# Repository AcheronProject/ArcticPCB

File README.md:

# Acheron 60-SM-S-STM32-MX-TH-WI (Codename "ArcticPCB")

See [this page](https://gondolindrim.github.io/AcheronDocs/arctic/intro.html) for the ArcticPCB documentation.

## Introduction

Arctic is an STM32F072-based universal 60% keyboard PCB featuring limited layouts and features. The layouts were cherry-picked by enthusiast ArcticFox and consist of only Tsangan bottom row. 

This PCB also features "relief" flex cuts aimed at improving keyboard typing feeling.

Arctic hold a very special place in my heart as it was one of the first two PCBs, together with the KeebsPCB, in the Acheron Project and effectively inaugurated it.

## Contributors

- Raphael "ArcticFox" Hochheim for helping choosing the compatible layouts
- Felipe 'MrKeebs" Coury who paid for the V1 prototypes and helped immensely by funding my learning
- PCBWay for sponsoring the pre-revision Alpha prototypes

## Supported layouts

Click [this link](http://www.keyboard-layout-editor.com/#/gists/73be427d3e8086a9253feece2dae6974) for the KLE file for the Arctic.

## Renders

Click at the images to zoom in.

Renders generated by the [tracespace.io](https://tracespace.io/view/) site.

## PCBWay sponsorship

The pre-revision Alpha of the ArcticPCB was sponsored by [PCBWay](http://www.pcbway.com), a big asian PCB manufacturer that provided prototypes for the Arctic.

The review article can be found at [the AcheronDocs page](https://gondolindrim.github.io/AcheronDocs/pcbway/sponsorship.html).

## Icon

The Fox icon was based on [this design](https://www.flaticon.com/free-icon/fox_112476) and slightly modified.

## Copyright notice

This project is released under the Acheron Open-Hardware License V1.2. For the license, please refer to the LICENCE.md file.

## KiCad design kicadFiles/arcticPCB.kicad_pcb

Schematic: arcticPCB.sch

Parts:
CB1: 1uF; C_0402_1005Metric
CB2: 10n; C_0402_1005Metric
CB3, CB5, CB8: 100n; C_0402_1005Metric
CB4, CB6: 4.7uF; C_0402_1005Metric
CB7: 100nF; C_0402_1005Metric
CRST1: 10u; C_0805_2012Metric_Pad1.15x1.40mm_HandSolder
CRST2: 4.7n; C_0805_2012Metric_Pad1.15x1.40mm_HandSolder
CSH1, CSH2: 4.7nF; C_0805_2012Metric
CSI1: 100n; C_0805_2012Metric_Pad1.15x1.40mm_HandSolder
CSO1: 100n; C_0805_2012Metric_Pad1.15x1.40mm_HandSolder
CUSB1: 100n; C_0805_2012Metric_Pad1.15x1.40mm_HandSolder
D1, D2, D3, D4, D5, D6, D7, D8, D9, D10, D11, D12, D13, D14, D15, D16, D17, D18, D19, D20, D21, D22, D23, D24, D25, D26, D27, D28, D29, D30, D31, D32, D33, D34, D35, D36, D37, D38, D39, D40, D41, D42, D43, D44, D45, D46, D47, D48, D49, D50, D51, D52, D53, D54, D55, D56, D57, D58, D59, D60, D62, D65: 1N4148; D_SOD-123
DF1: RB060M-60TR; D_SOD-123
DRST1: 1N4148; D_SOD-123
DS1: 1N4148; D_SOD-123
DSH1: 1N4007; D_SOD-123
F1: Polyfuse; Fuse_1812_4532
H1, H6: Half Side Hole; halfSideHole
H2: Mounting Hole; MoutingHole_Oval_7mm_5.0x2.5mm
H3, H4, H5, H7, H8, H9, H10: Oval Mounting Hole; MoutingHole_Oval_7mm_5.0x2.5mm
J1: TYPE-C-31-M12_13; TYPE-C-31-M-12
J2: Conn_01x14; PinHeader_1x14_P2.54mm_Vertical
J3: Conn_ARM_JTAG_SWD_10
L1: ArcticLogo; arcticLogoFilled
L2: OSHLogo; osh-logo
L3: Acheron Logo; acheronLong
L4: ArcticLabel; arcticLabel
L5: Acheron Logo; arcticLabelMask
QRST1: DTC123J; SOT-23
RCC1, RCC2: 5.1k; R_SMD_1026
RRST1: 100k; R_SMD_1026
RSH1, RSH2: 1M; R_SMD_1026
SW1: ESC; MX100
SW2: 1; MX100
SW3: 2; MX100
SW4: 3; MX100
SW5: 4; MX100
SW6: 5; MX100
SW7: 6; MX100
SW8: 7; MX100
SW9: 8; MX100
SW10: 9; MX100
SW11: 0; MX100
SW12: -_; MX100
SW13: +=; MX100
SW14: 2U BKSP; MX200
SW15: TAB_150; MX150
SW16: Q; MX100
SW17: W; MX100
SW18: E; MX100
SW19: R; MX100
SW20: T; MX100
SW21: Y; MX100
SW22: U; MX100
SW23: I; MX100
SW24: O; MX100
SW25: P; MX100
SW26: [{; MX100
SW27: ]}; MX100
SW28: \\|_150; MX150
SW29: CAPS_175; MX175
SW30: A; MX100
SW31: S; MX100
SW32: D; MX100
SW33: F; MX100
SW34: G; MX100
SW35: H; MX100
SW36: J; MX100
SW37: K; MX100
SW38: L; MX100
SW39: :;; MX100
SW40: \"'; MX100
SW41: ENTER_225; MX225R
SW42: LSHIFT_225; MX225
SW43: Z; MX100
SW44: X; MX100
SW45: C; MX100
SW46: V; MX100
SW47: B; MX100
SW48: N; MX100
SW49: M; MX100
SW50: <,; MX100
SW51: >.; MX100
SW52: ?/; MX100
SW53: RSHIFT_275; MX275
SW54: LCTRL_150; MX150
SW55: LGUI_100; MX100
SW56: LALT_150; MX150
SW57: SPACE_7U; MX700R
SW58: RALT_150; MX150
SW59: RGUI_100; MX100
SW60: RCTRL_150; MX150
SW61: FN_100; MX100
SW62: RSHIFT_175; MX175
SW63: STEPPED_CAPS_125; MX125
SW64: 1U LBKSP; MX100
SW65: 1U RBKSP; MX100
SWRST1: SW_Push; smdPushBtn
U1: STM32F072-LQFP48; LQFP-48_7x7mm_P0.5mm
U2: USBLC6-2SC6; SOT-23-6
U3: MCP1700-3302E_SOT23; SOT-23

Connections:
3.3V: CB1.2, CB2.2, CB3.2, CB4.2, CB5.2, CB6.2, CB7.1, CB8.2, CSO1.2, DS1.2 (A), J3.1 (VTref), SWRST1.1, U1.1 (VBAT), U1.9 (VDDA), U1.24 (VDD), U1.36 (VDDIO2), U1.48 (VDD), U3.2 (VO)
5V: CSI1.2, DF1.1 (K), DS1.1 (K), F1.1, U3.3 (VI)
/SHIELD: CSH1.2, J1.S (SHIELD), RSH1.1
BOOT0: CRST1.2, DRST1.1 (K), RRST1.1, U1.44 (BOOT0)
CASE: DSH1.2 (A), H8.1
Col1: SW1.1 (Col), SW15.1 (Col), SW29.1 (Col), SW42.1 (Col), SW54.1 (Col), SW63.1 (Col), U1.18 (PB0/TIM3_CH3/ADC_IN8)
Col2: SW2.1 (Col), SW16.1 (Col), SW30.1 (Col), SW43.1 (Col), SW55.1 (Col), U1.15 (PA5/ADC_IN5/DAC_OUT2)
Col3: SW3.1 (Col), SW17.1 (Col), SW31.1 (Col), SW44.1 (Col), SW56.1 (Col), U1.14 (PA4/TIM14_CH1/ADC_IN4)
Col4: SW4.1 (Col), SW18.1 (Col), SW32.1 (Col), SW45.1 (Col), U1.13 (PA3/TIM15_CH2/ADC_IN3)
Col5: SW5.1 (Col), SW19.1 (Col), SW33.1 (Col), SW46.1 (Col), U1.12 (PA2/ADC_IN2)
Col6: SW6.1 (Col), SW20.1 (Col), SW34.1 (Col), SW47.1 (Col), U1.11 (PA1/ADC_IN1)
Col7: SW7.1 (Col), SW21.1 (Col), SW35.1 (Col), SW48.1 (Col), SW57.1 (Col), U1.10 (PA0/ADC_IN0)
Col8: SW8.1 (Col), SW22.1 (Col), SW36.1 (Col), SW49.1 (Col), U1.6 (PF1/OSC_OUT)
Col9: SW9.1 (Col), SW23.1 (Col), SW37.1 (Col), SW50.1 (Col), U1.5 (PF0/OSC_IN)
Col10: SW10.1 (Col), SW24.1 (Col), SW38.1 (Col), SW51.1 (Col), SW58.1 (Col), U1.4 (PC15/OSC32_OUT)
Col11: SW11.1 (Col), SW25.1 (Col), SW39.1 (Col), SW52.1 (Col), SW59.1 (Col), U1.3 (PC14/OSC32_IN)
Col12: SW12.1 (Col), SW26.1 (Col), SW40.1 (Col), SW53.1 (Col), SW60.1 (Col), SW62.1 (Col), U1.2 (PC13)
Col13: SW13.1 (Col), SW27.1 (Col), SW41.1 (Col), SW61.1 (Col), U1.46 (SPI2_NSS/I2S2_WS/I2C1_SDA/TIM17_CH1/PB9)
Col14: SW14.1 (Col), SW28.1 (Col), SW64.1 (Col), SW65.1 (Col), U1.45 (I2C1_SCL/TIM16_CH1/PB8)
D+: U1.33 (USB_DP/PA12), U2.3 (IO2)
D-: U1.32 (USB_DM/TIM1_CH4/PA11), U2.1 (IO1)
DBus+: J1.A6 (D+), J1.B6 (D+), U2.4 (IO2)
DBus-: J1.A7 (D-), J1.B7 (D-), U2.6 (IO1)
Extra1: J2.1, U1.41 (SPI1_MOSI/I2S1_SD/TIM3_CH2/PB5)
Extra2: J2.2, U1.40 (SPI1_MISO/I2S1_MCK/TIM3_CH1/PB4)
Extra3: J2.3, U1.39 (SPI1_SCK/I2S1_CK/TIM2_CH2/PB3)
Extra4: J2.4, U1.38 (PA2)
Extra5: J2.5, U1.31 (TIM1_CH3/PA10)
Extra6: J2.6, U1.30 (TIM1_CH2/PA9)
Extra7: J2.7, U1.29 (TIM1_CH1/PA8)
Extra8: J2.8, U1.28 (SPI2_MOSI/I2S2_SD/PB15)
Extra9: J2.9, U1.27 (PB14/SPI2_MISO/I2S2_MCK/I2C2_SDA/TIM15_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)
Extra10: J2.10, U1.26 (SPI2_SCK/I2S2_CK/I2C2_SCL/PB13)
Extra11: J2.11, U1.25 (PB12)
Extra12: J2.12, U1.22 (PB11/TIM2_CH4/I2C2_SDA)
Extra13: J2.13, U1.21 (PB10/SPI2_SCK/I2C2_SCL/TIM2_CH3)
Extra14: J2.14, U1.20 (PB2)
GND: CB1.1, CB2.1, CB3.1, CB4.1, CB5.1, CB6.1, CB7.2, CB8.1, CRST1.1, CRST2.2, CSH1.1, CSH2.1, CSI1.1, CSO1.1, CUSB1.1, DF1.2 (A), J1.A1 (GND), J1.B1 (GND), J3.3 (GND), J3.5 (GND), J3.9 (GNDDetect), QRST1.2 (E), RCC1.1, RCC2.1, RRST1.2, RSH1.2, RSH2.2, U1.8 (VSSA), U1.23 (VSS), U1.35 (VSS), U1.47 (VSS), U2.2 (GND), U3.1 (GND)
NRST: CRST2.1, J3.10 (~RESET~), QRST1.3 (C), U1.7 (NRST)
unnamed: CSH2.2, DSH1.1 (K), RSH2.1
unnamed: D1.2 (A), SW1.2 (Row)
unnamed: D2.2 (A), SW2.2 (Row)
unnamed: D3.2 (A), SW3.2 (Row)
unnamed: D4.2 (A), SW4.2 (Row)
unnamed: D5.2 (A), SW5.2 (Row)
unnamed: D6.2 (A), SW6.2 (Row)
unnamed: D7.2 (A), SW7.2 (Row)
unnamed: D8.2 (A), SW8.2 (Row)
unnamed: D9.2 (A), SW9.2 (Row)
unnamed: D10.2 (A), SW10.2 (Row)
unnamed: D11.2 (A), SW11.2 (Row)
unnamed: D12.2 (A), SW12.2 (Row)
unnamed: D13.2 (A), SW13.2 (Row)
unnamed: D14.2 (A), SW14.2 (Row), SW64.2 (Row)
unnamed: D15.2 (A), SW15.2 (Row)
unnamed: D16.2 (A), SW16.2 (Row)
unnamed: D17.2 (A), SW17.2 (Row)
unnamed: D18.2 (A), SW18.2 (Row)
unnamed: D19.2 (A), SW19.2 (Row)
unnamed: D20.2 (A), SW20.2 (Row)
unnamed: D21.2 (A), SW21.2 (Row)
unnamed: D22.2 (A), SW22.2 (Row)
unnamed: D23.2 (A), SW23.2 (Row)
unnamed: D24.2 (A), SW24.2 (Row)
unnamed: D25.2 (A), SW25.2 (Row)
unnamed: D26.2 (A), SW26.2 (Row)
unnamed: D27.2 (A), SW27.2 (Row)
unnamed: D28.2 (A), SW28.2 (Row)
unnamed: D29.2 (A), SW29.2 (Row), SW63.2 (Row)
unnamed: D30.2 (A), SW30.2 (Row)
unnamed: D31.2 (A), SW31.2 (Row)
unnamed: D32.2 (A), SW32.2 (Row)
unnamed: D33.2 (A), SW33.2 (Row)
unnamed: D34.2 (A), SW34.2 (Row)
unnamed: D35.2 (A), SW35.2 (Row)
unnamed: D36.2 (A), SW36.2 (Row)
unnamed: D37.2 (A), SW37.2 (Row)
unnamed: D38.2 (A), SW38.2 (Row)
unnamed: D39.2 (A), SW39.2 (Row)
unnamed: D40.2 (A), SW40.2 (Row)
unnamed: D41.2 (A), SW41.2 (Row)
unnamed: D42.2 (A), SW42.2 (Row)
unnamed: D43.2 (A), SW43.2 (Row)
unnamed: D44.2 (A), SW44.2 (Row)
unnamed: D45.2 (A), SW45.2 (Row)
unnamed: D46.2 (A), SW46.2 (Row)
unnamed: D47.2 (A), SW47.2 (Row)
unnamed: D48.2 (A), SW48.2 (Row)
unnamed: D49.2 (A), SW49.2 (Row)
unnamed: D50.2 (A), SW50.2 (Row)
unnamed: D51.2 (A), SW51.2 (Row)
unnamed: D52.2 (A), SW52.2 (Row)
unnamed: D53.2 (A), SW61.2 (Row)
unnamed: D54.2 (A), SW54.2 (Row)
unnamed: D55.2 (A), SW55.2 (Row)
unnamed: D56.2 (A), SW56.2 (Row)
unnamed: D57.2 (A), SW57.2 (Row)
unnamed: D58.2 (A), SW58.2 (Row)
unnamed: D59.2 (A), SW59.2 (Row)
unnamed: D60.2 (A), SW60.2 (Row)
unnamed: D62.2 (A), SW53.2 (Row), SW62.2 (Row)
unnamed: D65.2 (A), SW65.2 (Row)
unnamed: DRST1.2 (A), QRST1.1 (B), SWRST1.2
unnamed: J1.A5 (CC1), RCC2.2
unnamed: J1.B5 (CC2), RCC1.2
Row1: D1.1 (K), D2.1 (K), D3.1 (K), D4.1 (K), D5.1 (K), D6.1 (K), D7.1 (K), D8.1 (K), D9.1 (K), D10.1 (K), D11.1 (K), D12.1 (K), D13.1 (K), D14.1 (K), U1.43 (2C1_SDA/PB7)
Row2: D15.1 (K), D16.1 (K), D17.1 (K), D18.1 (K), D19.1 (K), D20.1 (K), D21.1 (K), D22.1 (K), D23.1 (K), D24.1 (K), D25.1 (K), D26.1 (K), D27.1 (K), D28.1 (K), U1.42 (I2C1_SCL/PB6)
Row3: D29.1 (K), D30.1 (K), D31.1 (K), D32.1 (K), D33.1 (K), D34.1 (K), D35.1 (K), D36.1 (K), D37.1 (K), D38.1 (K), D39.1 (K), D40.1 (K), D41.1 (K), D65.1 (K), U1.16 (PA6/ADC_IN6/TIM3_CH1/TIM16_CH1)
Row4: D42.1 (K), D43.1 (K), D44.1 (K), D45.1 (K), D46.1 (K), D47.1 (K), D48.1 (K), D49.1 (K), D50.1 (K), D51.1 (K), D52.1 (K), D53.1 (K), D62.1 (K), U1.17 (PA7/TIM3_CH2/TIM14_CH1/ADC_IN7)
Row5: D54.1 (K), D55.1 (K), D56.1 (K), D57.1 (K), D58.1 (K), D59.1 (K), D60.1 (K), U1.19 (PB1/TIM3_CH4/TIM14_CH1/ADC_IN9)
SWCLK: J3.4 (SWDCLK/TCK), U1.37 (SWCLK/PA14)
SWDIO: J3.2 (SWDIO/TMS), U1.34 (SWDIO/PA13)
VBUS: CUSB1.2, F1.2, J1.A4 (VBUS), J1.B4 (VBUS), U2.5 (VBUS)

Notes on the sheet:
REFERENCES
[1] STM32F072x8 / STM32F072xB datasheet
https://www.st.com/resource/en/datasheet/stm32f072rb.pdf
[2] AN4080 Application note
https://www.st.com/content/ccc/resource/technical/document/application_note/c9/19/d7/b8/6b/0e/4c/d3/DM00051986.pdf/files/DM00051986.pdf/jcr:content/translations/en.DM00051986.pdf
Switch matrix
Logos and flags
Mounting holes
Shield
USB Connector
USD ESD
Power supply and protection circuit
Serial programming
Hard reset circuit
Case ESD
Extra pins
CBx are the bypass capacitors. Their value is specified in reference [2].
MCU

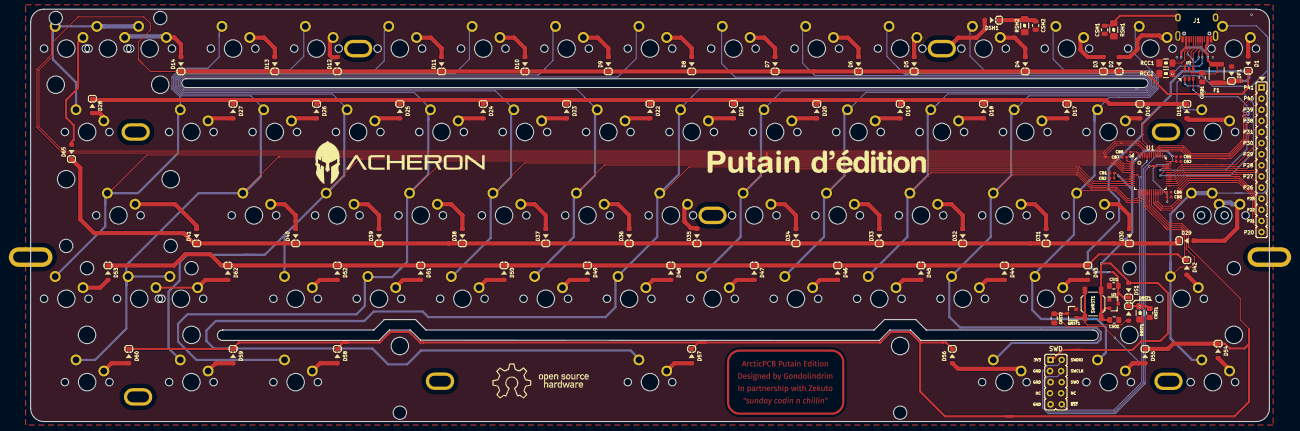
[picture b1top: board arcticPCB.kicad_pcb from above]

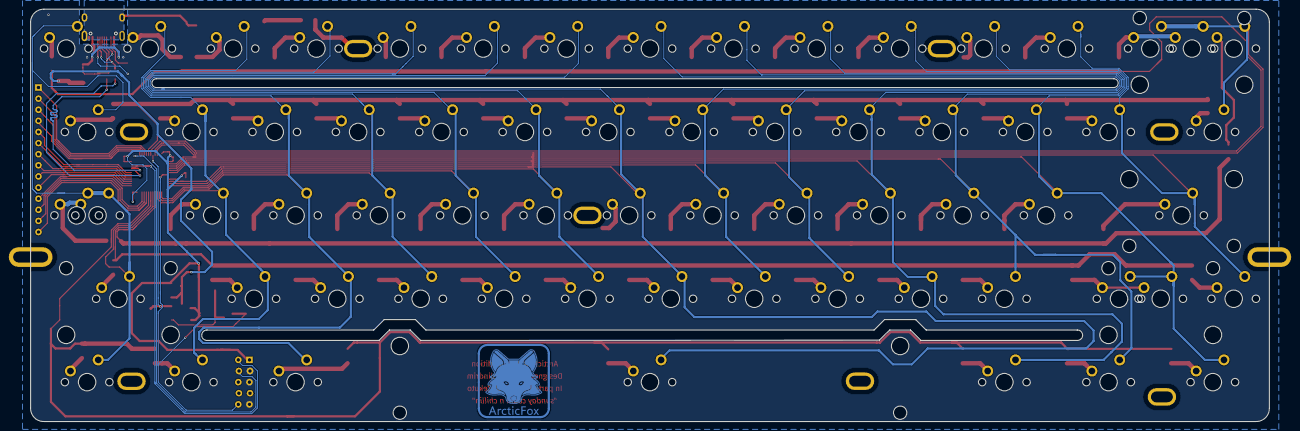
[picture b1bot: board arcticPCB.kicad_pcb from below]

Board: 2 copper layers, 283.0 x 94.2 mm, 176 parts (7 on the bottom side), 113 nets.

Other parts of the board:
L6: Putain Logo; putainLogo_50_5

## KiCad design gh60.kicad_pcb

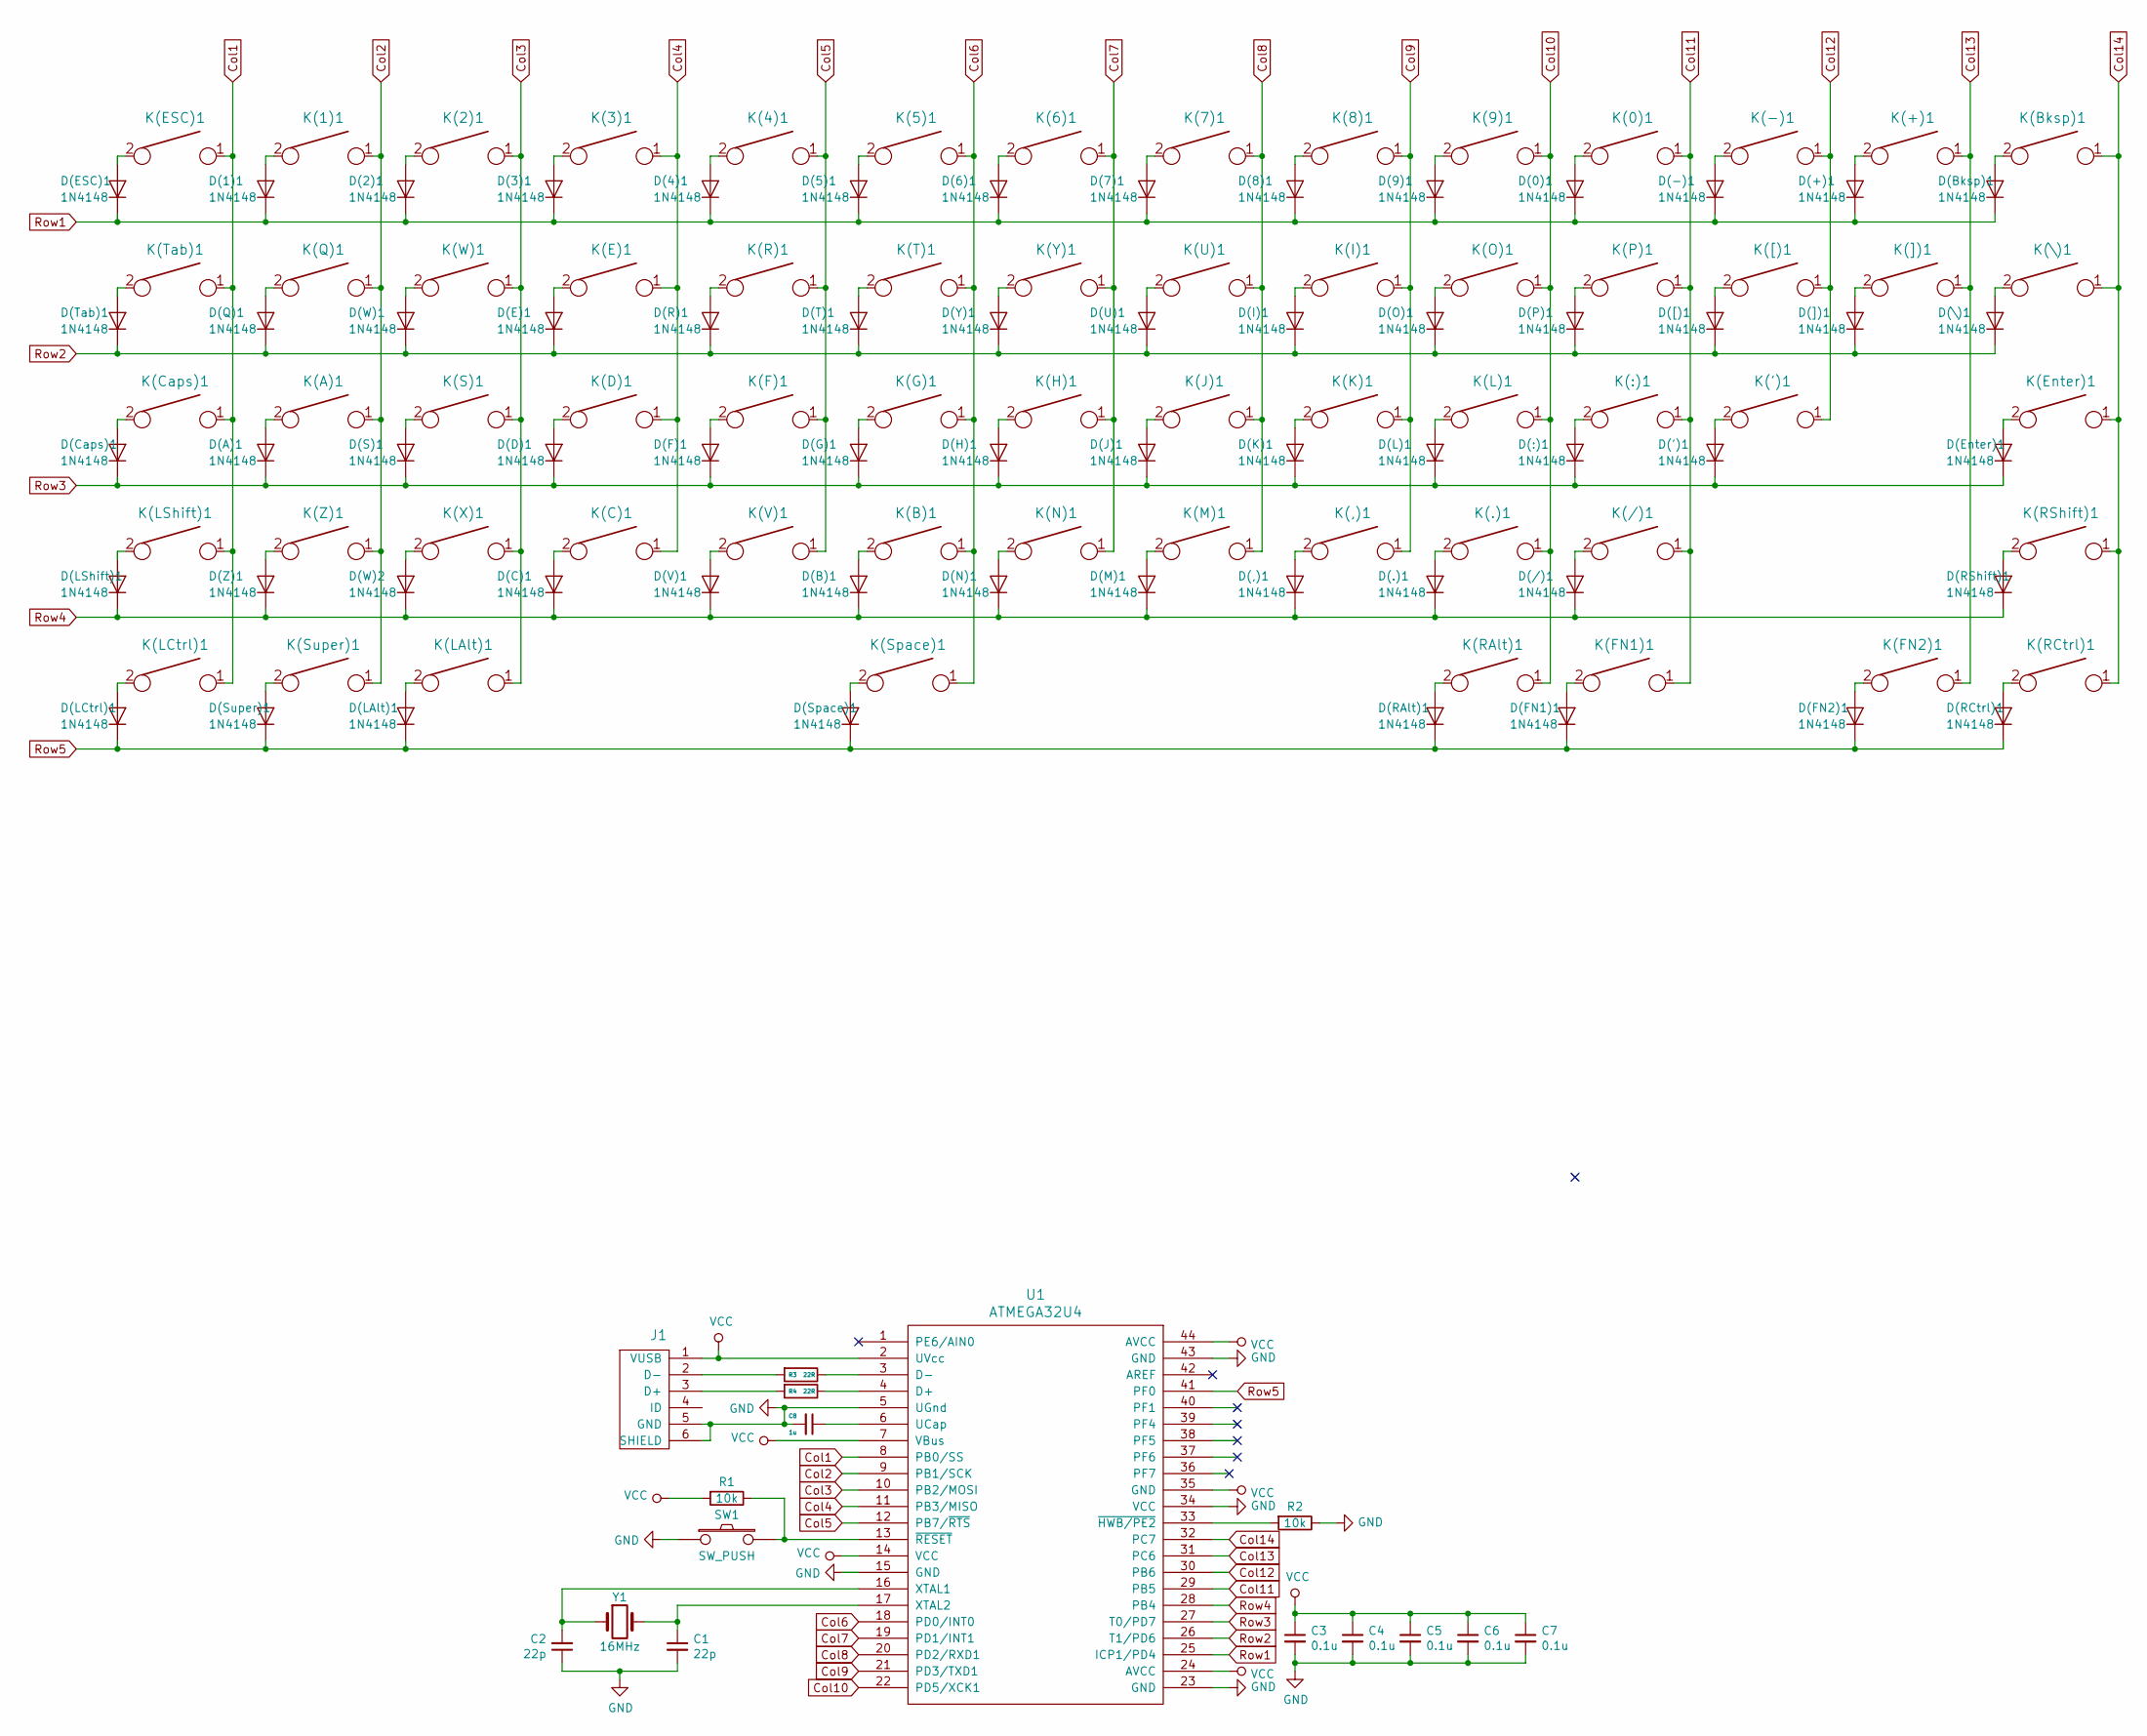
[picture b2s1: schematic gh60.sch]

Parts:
C1, C2: 22p; C_0805_2012Metric_Pad1.15x1.40mm_HandSolder
C3, C4, C5, C6, C7: 0.1u; C_0805_2012Metric_Pad1.15x1.40mm_HandSolder
C8: 1u; C_0805_2012Metric_Pad1.15x1.40mm_HandSolder
D(0)1, D(1)1, D(2)1, D(3)1, D(4)1, D(5)1, D(6)1, D(7)1, D(8)1, D(9)1, D(.)1: 1N4148; D_SOD123_axial
D(')1: 1N4148; D_SOD123_axial
D(+)1: 1N4148; D_SOD123_axial
D(,)1: 1N4148; D_SOD123_axial
D(-)1: 1N4148; D_SOD123_axial
D(/)1: 1N4148; D_SOD123_axial
D(:)1: 1N4148; D_SOD123_axial
D(A)1: 1N4148; D_SOD123_axial
D(B)1: 1N4148; D_SOD123_axial
D(Bksp)1: 1N4148; D_SOD123_axial
D(C)1: 1N4148; D_SOD123_axial
D(Caps)1: 1N4148; D_SOD123_axial
D(D)1: 1N4148; D_SOD123_axial
D(E)1: 1N4148; D_SOD123_axial
D(ESC)1: 1N4148; D_SOD123_axial
D(Enter)1: 1N4148; D_SOD123_axial
D(F)1: 1N4148; D_SOD123_axial
D(FN1)1, D(FN2)1: 1N4148; D_SOD123_axial
D(G)1: 1N4148; D_SOD123_axial
D(H)1: 1N4148; D_SOD123_axial
D(I)1: 1N4148; D_SOD123_axial
D(J)1: 1N4148; D_SOD123_axial
D(K)1: 1N4148; D_SOD123_axial
D(L)1: 1N4148; D_SOD123_axial
D(LAlt)1: 1N4148; D_SOD123_axial
D(LCtrl)1: 1N4148; D_SOD123_axial
D(LShift)1: 1N4148; D_SOD123_axial
D(M)1: 1N4148; D_SOD123_axial
D(N)1: 1N4148; D_SOD123_axial
D(O)1: 1N4148; D_SOD123_axial
D(P)1: 1N4148; D_SOD123_axial
D(Q)1: 1N4148; D_SOD123_axial
D(R)1: 1N4148; D_SOD123_axial
D(RAlt)1: 1N4148; D_SOD123_axial
D(RCtrl)1: 1N4148; D_SOD123_axial
D(RShift)1: 1N4148; D_SOD123_axial
D(S)1: 1N4148; D_SOD123_axial
D(Space)1: 1N4148; D_SOD123_axial
D(Super)1: 1N4148; D_SOD123_axial
D(T)1: 1N4148; D_SOD123_axial
D(Tab)1: 1N4148; D_SOD123_axial
D(U)1: 1N4148; D_SOD123_axial
D(V)1: 1N4148; D_SOD123_axial
D(W)1, D(W)2: 1N4148; D_SOD123_axial
D(Y)1: 1N4148; D_SOD123_axial
D(Z)1: 1N4148; D_SOD123_axial
D([)1: 1N4148; D_SOD123_axial
D(\)1: 1N4148; D_SOD123_axial
D(])1: 1N4148; D_SOD123_axial
J1: USB_mini_micro_B; USB_miniB_hirose_5S8
K(0)1, K(1)1, K(2)1, K(3)1, K(4)1, K(5)1, K(6)1, K(7)1, K(8)1, K(9)1, K(.)1: KEYSW; Mx_Alps_100
K(')1: KEYSW; Mx_Alps_100
K(+)1: KEYSW; Mx_Alps_100
K(,)1: KEYSW; Mx_Alps_100
K(-)1: KEYSW; Mx_Alps_100
K(/)1: KEYSW; Mx_Alps_100
K(:)1: KEYSW; Mx_Alps_100
K(A)1: KEYSW; Mx_Alps_100
K(B)1: KEYSW; Mx_Alps_100
K(Bksp)1: KEYSW; Mx_Alps_200
K(C)1: KEYSW; Mx_Alps_100
K(Caps)1: KEYSW; Mx_Alps_175
K(D)1: KEYSW; Mx_Alps_100
K(E)1: KEYSW; Mx_Alps_100
K(ESC)1: KEYSW; Mx_Alps_100
K(Enter)1: KEYSW; Mx_Alps_225
K(F)1: KEYSW; Mx_Alps_100
K(FN1)1, K(FN2)1: KEYSW; Mx_Alps_125
K(G)1: KEYSW; Mx_Alps_100
K(H)1: KEYSW; Mx_Alps_100
K(I)1: KEYSW; Mx_Alps_100
K(J)1: KEYSW; Mx_Alps_100
K(K)1: KEYSW; Mx_Alps_100
K(L)1: KEYSW; Mx_Alps_100
K(LAlt)1: KEYSW; Mx_Alps_125
K(LCtrl)1: KEYSW; Mx_Alps_125
K(LShift)1: KEYSW; Mx_Alps_225
K(M)1: KEYSW; Mx_Alps_100
K(N)1: KEYSW; Mx_Alps_100
K(O)1: KEYSW; Mx_Alps_100
K(P)1: KEYSW; Mx_Alps_100
K(Q)1: KEYSW; Mx_Alps_100
K(R)1: KEYSW; Mx_Alps_100
K(RAlt)1: KEYSW; Mx_Alps_125
K(RCtrl)1: KEYSW; Mx_Alps_125
K(RShift)1: KEYSW; Mx_Alps_275
K(S)1: KEYSW; Mx_Alps_100
K(Space)1: KEYSW; Mx_Alps_625
K(Super)1: KEYSW; Mx_Alps_125
K(T)1: KEYSW; Mx_Alps_100
K(Tab)1: KEYSW; Mx_Alps_150
K(U)1: KEYSW; Mx_Alps_100
K(V)1: KEYSW; Mx_Alps_100
K(W)1: KEYSW; Mx_Alps_100
K(X)1: KEYSW; Mx_Alps_100
K(Y)1: KEYSW; Mx_Alps_100
K(Z)1: KEYSW; Mx_Alps_100
K([)1: KEYSW; Mx_Alps_100
K(\)1: KEYSW; Mx_Alps_150
K(])1: KEYSW; Mx_Alps_100
R1, R2: 10k; R_0805_2012Metric_Pad1.15x1.40mm_HandSolder
R3, R4: 22R; R_0805_2012Metric_Pad1.15x1.40mm_HandSolder
SW1: SW_PUSH; SW_SPST_TL3342
U1: ATMEGA32U4; TQFP-44_10x10mm_P0.8mm
Y1: 16MHz; Crystal_SMD_5032-2Pin_5.0x3.2mm_HandSoldering

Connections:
Col1: K(Caps)1.1, K(ESC)1.1, K(LCtrl)1.1, K(LShift)1.1, K(Tab)1.1, U1.8 (PB0/SS)
Col2: K(1)1.1, K(A)1.1, K(Q)1.1, K(Super)1.1, K(Z)1.1, U1.9 (PB1/SCK)
Col3: K(2)1.1, K(LAlt)1.1, K(S)1.1, K(W)1.1, K(X)1.1, U1.10 (PB2/MOSI)
Col4: K(3)1.1, K(C)1.1, K(D)1.1, K(E)1.1, U1.11 (PB3/MISO)
Col5: K(4)1.1, K(F)1.1, K(R)1.1, K(V)1.1, U1.12 (PB7/~RTS)
Col6: K(5)1.1, K(B)1.1, K(G)1.1, K(Space)1.1, K(T)1.1, U1.18 (PD0/INT0)
Col7: K(6)1.1, K(H)1.1, K(N)1.1, K(Y)1.1, U1.19 (PD1/INT1)
Col8: K(7)1.1, K(J)1.1, K(M)1.1, K(U)1.1, U1.20 (PD2/RXD1)
Col9: K(8)1.1, K(,)1.1, K(I)1.1, K(K)1.1, U1.21 (PD3/TXD1)
Col10: K(9)1.1, K(.)1.1, K(L)1.1, K(O)1.1, K(RAlt)1.1, U1.22 (PD5/XCK1)
Col11: K(0)1.1, K(/)1.1, K(:)1.1, K(FN1)1.1, K(P)1.1, U1.29 (PB5)
Col12: K(')1.1, K(-)1.1, K([)1.1, U1.30 (PB6)
Col13: K(+)1.1, K(FN2)1.1, K(])1.1, U1.31 (PC6)
Col14: K(Bksp)1.1, K(Enter)1.1, K(RCtrl)1.1, K(RShift)1.1, K(\)1.1, U1.32 (PC7)
GND: C1.2, C2.1, C3.2, C4.2, C5.2, C6.2, C7.2, C8.2, J1.5 (GND), J1.6 (SHIELD), R2.1, SW1.1, U1.5 (UGnd), U1.15 (GND), U1.23 (GND), U1.34 (VCC), U1.43 (GND)
unnamed: C1.1, U1.17 (XTAL2), Y1.2
unnamed: C2.2, U1.16 (XTAL1), Y1.1
unnamed: C8.1, U1.6 (UCap)
unnamed: D(0)1.2 (A), K(0)1.2
unnamed: D(1)1.2 (A), K(1)1.2
unnamed: D(2)1.2 (A), K(2)1.2
unnamed: D(3)1.2 (A), K(3)1.2
unnamed: D(4)1.2 (A), K(4)1.2
unnamed: D(5)1.2 (A), K(5)1.2
unnamed: D(6)1.2 (A), K(6)1.2
unnamed: D(7)1.2 (A), K(7)1.2
unnamed: D(8)1.2 (A), K(8)1.2
unnamed: D(9)1.2 (A), K(9)1.2
unnamed: D(')1.2 (A), K(')1.2
unnamed: D(+)1.2 (A), K(+)1.2
unnamed: D(,)1.2 (A), K(,)1.2
unnamed: D(-)1.2 (A), K(-)1.2
unnamed: D(.)1.2 (A), K(.)1.2
unnamed: D(/)1.2 (A), K(/)1.2
unnamed: D(:)1.2 (A), K(:)1.2
unnamed: D(A)1.2 (A), K(A)1.2
unnamed: D(B)1.2 (A), K(B)1.2
unnamed: D(Bksp)1.2 (A), K(Bksp)1.2
unnamed: D(C)1.2 (A), K(C)1.2
unnamed: D(Caps)1.2 (A), K(Caps)1.2
unnamed: D(D)1.2 (A), K(D)1.2
unnamed: D(E)1.2 (A), K(E)1.2
unnamed: D(ESC)1.2 (A), K(ESC)1.2
unnamed: D(Enter)1.2 (A), K(Enter)1.2
unnamed: D(F)1.2 (A), K(F)1.2
unnamed: D(FN1)1.2 (A), K(FN1)1.2
unnamed: D(FN2)1.2 (A), K(FN2)1.2
unnamed: D(G)1.2 (A), K(G)1.2
unnamed: D(H)1.2 (A), K(H)1.2
unnamed: D(I)1.2 (A), K(I)1.2
unnamed: D(J)1.2 (A), K(J)1.2
unnamed: D(K)1.2 (A), K(K)1.2
unnamed: D(L)1.2 (A), K(L)1.2
unnamed: D(LAlt)1.2 (A), K(LAlt)1.2
unnamed: D(LCtrl)1.2 (A), K(LCtrl)1.2
unnamed: D(LShift)1.2 (A), K(LShift)1.2
unnamed: D(M)1.2 (A), K(M)1.2
unnamed: D(N)1.2 (A), K(N)1.2
unnamed: D(O)1.2 (A), K(O)1.2
unnamed: D(P)1.2 (A), K(P)1.2
unnamed: D(Q)1.2 (A), K(Q)1.2
unnamed: D(R)1.2 (A), K(R)1.2
unnamed: D(RAlt)1.2 (A), K(RAlt)1.2
unnamed: D(RCtrl)1.2 (A), K(RCtrl)1.2
unnamed: D(RShift)1.2 (A), K(RShift)1.2
unnamed: D(S)1.2 (A), K(S)1.2
unnamed: D(Space)1.2 (A), K(Space)1.2
unnamed: D(Super)1.2 (A), K(Super)1.2
unnamed: D(T)1.2 (A), K(T)1.2
unnamed: D(Tab)1.2 (A), K(Tab)1.2
unnamed: D(U)1.2 (A), K(U)1.2
unnamed: D(V)1.2 (A), K(V)1.2
unnamed: D(W)1.2 (A), K(W)1.2
unnamed: D(W)2.2 (A), K(X)1.2
unnamed: D(Y)1.2 (A), K(Y)1.2
unnamed: D(Z)1.2 (A), K(Z)1.2
unnamed: D([)1.2 (A), K([)1.2
unnamed: D(\)1.2 (A), K(\)1.2
unnamed: D(])1.2 (A), K(])1.2
unnamed: J1.2 (D-), R3.2
unnamed: J1.3 (D+), R4.2
unnamed: R1.1, SW1.2, U1.13 (~RESET)
unnamed: R2.2, U1.33 (~HWB/PE2)
unnamed: R3.1, U1.3 (D-)
unnamed: R4.1, U1.4 (D+)
Row1: D(0)1.1 (K), D(1)1.1 (K), D(2)1.1 (K), D(3)1.1 (K), D(4)1.1 (K), D(5)1.1 (K), D(6)1.1 (K), D(7)1.1 (K), D(8)1.1 (K), D(9)1.1 (K), D(+)1.1 (K), D(-)1.1 (K), D(Bksp)1.1 (K), D(ESC)1.1 (K), U1.25 (ICP1/PD4)
Row2: D(E)1.1 (K), D(I)1.1 (K), D(O)1.1 (K), D(P)1.1 (K), D(Q)1.1 (K), D(R)1.1 (K), D(T)1.1 (K), D(Tab)1.1 (K), D(U)1.1 (K), D(W)1.1 (K), D(Y)1.1 (K), D([)1.1 (K), D(\)1.1 (K), D(])1.1 (K), U1.26 (T1/PD6)
Row3: D(')1.1 (K), D(:)1.1 (K), D(A)1.1 (K), D(Caps)1.1 (K), D(D)1.1 (K), D(Enter)1.1 (K), D(F)1.1 (K), D(G)1.1 (K), D(H)1.1 (K), D(J)1.1 (K), D(K)1.1 (K), D(L)1.1 (K), D(S)1.1 (K), U1.27 (T0/PD7)
Row4: D(,)1.1 (K), D(.)1.1 (K), D(/)1.1 (K), D(B)1.1 (K), D(C)1.1 (K), D(LShift)1.1 (K), D(M)1.1 (K), D(N)1.1 (K), D(RShift)1.1 (K), D(V)1.1 (K), D(W)2.1 (K), D(Z)1.1 (K), U1.28 (PB4)
Row5: D(FN1)1.1 (K), D(FN2)1.1 (K), D(LAlt)1.1 (K), D(LCtrl)1.1 (K), D(RAlt)1.1 (K), D(RCtrl)1.1 (K), D(Space)1.1 (K), D(Super)1.1 (K), U1.41 (PF0)
VCC: C3.1, C4.1, C5.1, C6.1, C7.1, J1.1 (VUSB), R1.2, U1.2 (UVcc), U1.7 (VBus), U1.14 (VCC), U1.24 (AVCC), U1.35 (GND), U1.44 (AVCC)

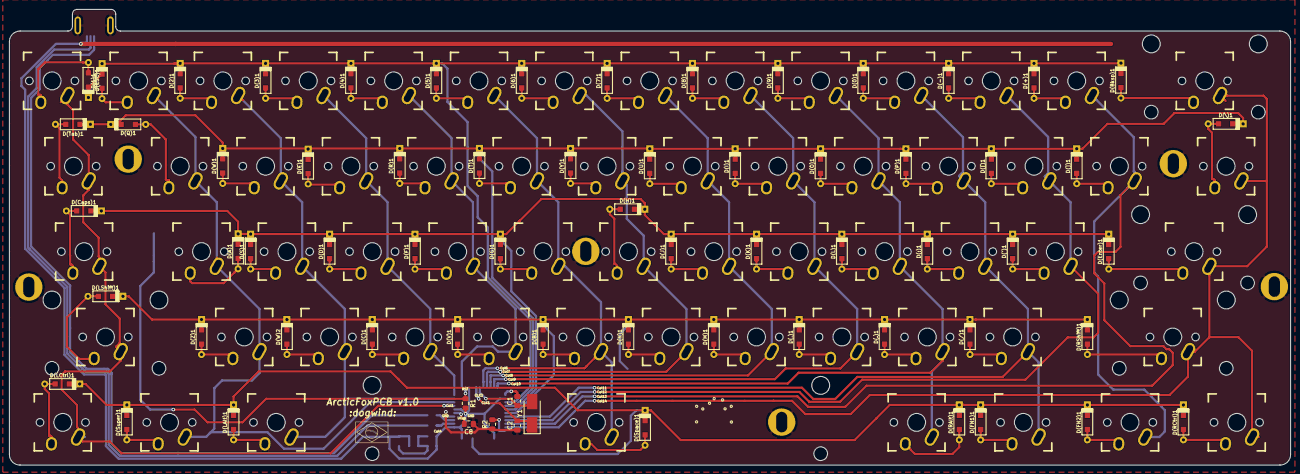
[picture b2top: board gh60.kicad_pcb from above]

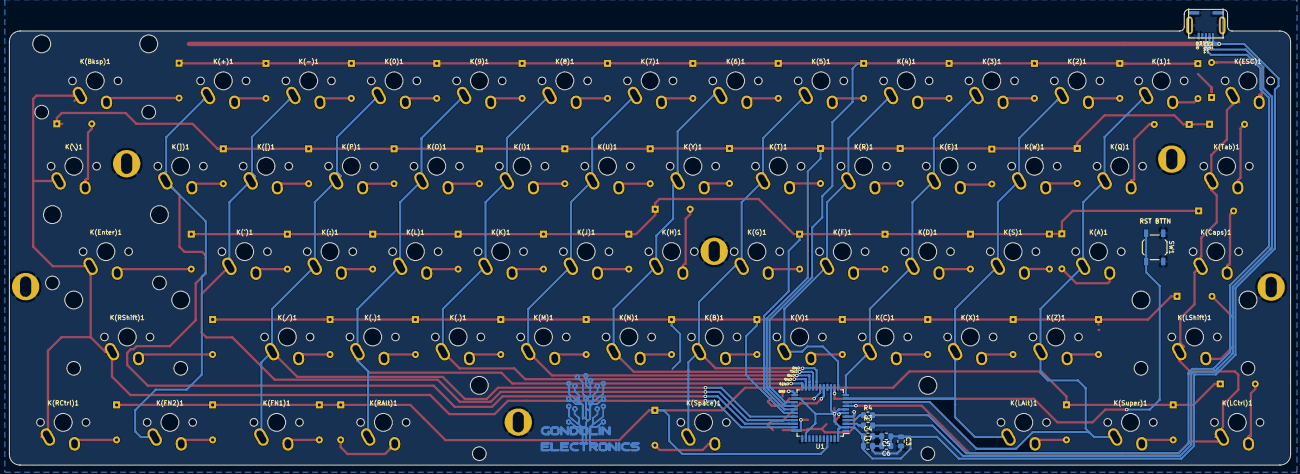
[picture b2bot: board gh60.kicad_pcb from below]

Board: 2 copper layers, 285.8 x 101.7 mm, 144 parts (10 on the bottom side), 91 nets.

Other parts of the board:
Poker_oval_hole: VAL**; Poker_oval_hole
Poker_oval_hole#2, Poker_oval_hole#3, Poker_oval_hole#4, Poker_oval_hole#5, Poker_oval_hole#6: VAL**; Poker_oval_hole

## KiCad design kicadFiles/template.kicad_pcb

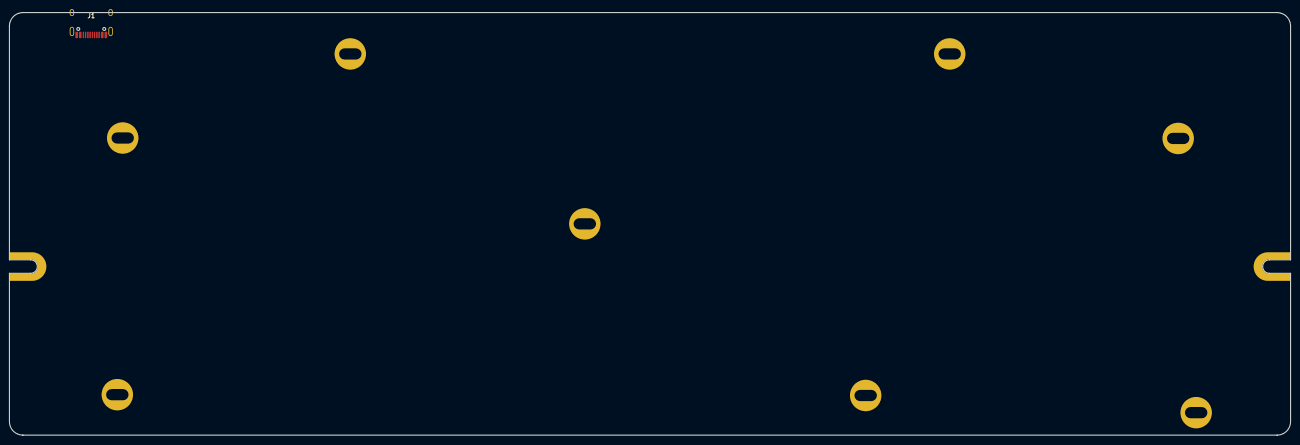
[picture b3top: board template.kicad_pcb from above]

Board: 2 copper layers, 285.0 x 94.0 mm, 11 parts (0 on the bottom side), 5 nets, no tracks yet.

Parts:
H1, H6: Half Side Hole; halfSideHole
H2: Mounting Hole; MoutingHole_Oval_7mm_5.0x2.5mm
H3, H4, H5, H7, H8, H9, H10: Oval Mounting Hole; MoutingHole_Oval_7mm_5.0x2.5mm
J1: TYPE-C-31-M12_13; TYPE-C-31-M-12

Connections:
DBus+: J1.A7, J1.B7
DBus-: J1.A6, J1.B6
GND: J1.A1, J1.B1
unnamed: J1.A5, J1.B5
VBUS: J1.A4, J1.B4

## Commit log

2018-12-15 Added logo
2018-12-21 Added pertinent PCB design articles
2019-02-10 Used SharkPCB schematic as canvas
2019-02-28 Revamped README and started V2
2019-03-15 [Base] Added dimensions and mounting holes
2019-07-30 [Update] Places some switches
2019-07-30 [Update] Finished placing switches, placed logo
2019-07-31 [Update] Added 1mm clearance to mounting holes and added ground planes
2019-07-31 [Update,Feature] Added flex cuts, routed and placed most components
2019-08-01 [Update] Finished routing
2019-08-01 [Update] Added mounting holes ESD protection
2019-08-01 [Update] Added new readme and license
2019-08-16 Adusted FoxLogo for Bitbucket avatar
2019-08-16 Updated license to AOHL V1.1
    This license features a better, clearer text in some points and was changed from reestructuredText to Markdown.
2019-08-16 Added new license
2019-08-16 Updated README logo
2019-08-20 Added 3D models and Blender file
    - STEP and VMRL models of the current PCB were added to the 3D_Models folder.
    - Using the VMRL a Blender file was added to the blender folder. This file contains only some renaming and a camera configuration for the scene, adding materials and appearances is still needed.
2019-09-02 Added RCC2
    - The PCB used a single pulldown resistor for both CC1 and CC2 pins of the USB connector, which is not the right way to do it. This has been fixed and now each CC pin has a single resistor.
2019-09-18 Add extra pins, organize schematic, add renders
    - There were two pins in the PCB that were left unused and un-exposed to use. Now those two pins are broken out so they can be used. To execute this, some cols and rows had to have their pins realloc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
    - Schematic is better organized;
    - Added KLE and PCB renders at the REAME file.
2019-09-18 Fix broken image link on README
2019-09-19 Update AcheronLibrary submodule
2019-09-20 Optimize routing, move SWD pins
2019-09-20 Reorganize graphics, optimize routing
    - The ./graphics folder was reorganized
    - Some traces, specially the ones leading to SWD pins, were re-done for
    efficiency and optimization
2019-09-20 Update: update renders
2019-09-20 Update Library, improve footprints and label
    - The label was previously written "release Alpha" which is not the case (this is still version pre-Alpha);
    - New MX_SolderMask witch footprints from the AcheronLibrary
    - The extra pins were allocated into three symbols (J2, J3 and J4). These were grouped under the same J2, having 14 pins and an improved footprint;
    - Optimized routing near the MCU area;
    - Added more clearance to the D+/D- differential pair to make sure it is free from interference;
2019-09-21 Add new pin header footprints
    - The AcheronLibrary pin header footprints were updated, and a SWD JTAG
    footprint was added (see AcheronLibrary commit 280b825).
    - Following this, the pin header footprints on Arctic were redone and
    the JTAG footprint was added.
2019-09-21 Improved diff. pair pad clearances
    - The differential pair D-/D+ has a 20thou clearance, which was used by
    KiCad for the pads on USBLC6 (U2) and the microprocessor (U1), making
    the filled zones around those pads not so good. The net clearance of
    20thou remains, although the pads now have a normal clearance of 6 thou.
2019-09-21 Continue improvements from last commit.
2019-09-21 Add TODO file
2019-09-21 Update: refresh renders
2019-09-22 Update: fixed naming of top row
2019-09-22 Fix: problem of RALT key placement
2019-09-23 Fix: problem with GND pour and Col7 routing
2019-09-23 Update: README renders
2019-12-17 Updated README for sponsorship
2020-01-18 Fiz RShift / Enter stab collision issue
    - The RShift and Enter stabs were positioned in a way that they would collide. The Enter stab was rotated to avoid this.
2020-03-18 Solve pre-Alpha prototype issues
    This commit solves the issues found in the pre-Alpha prototypes:
    - In the USB connector, the D+ and D- pads were switched; this has been fixed and the differential pair routing was improved;
    - The split Right Shift keyswitches SW62 for the 1.75U RShift and 1U SW61 for the Fn were in the wrong orientation: the Fn key SW61 was on the left and SW62 was on the left. They were swapped for the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
    - Also, to make firmware definitions easier, the 1.75U RShift key and 2.75U RShift key are now at the same position, whereas in pre-Alpha SW62 for the 1.75RShift was at the same position with SW61 fo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
2020-03-18 Refresh renders for rev Alpha
2020-04-15 Updated files and README
2020-04-15 Updated renders
2020-06-04 fix: fix typo on funding
